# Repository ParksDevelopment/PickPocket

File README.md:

# 2Pocket

[Introduction](#Introduction)

[Info and Production](#Production)

[PCB](#PCB)

[Firmware](#Firmware)

[Case](#Case)

[Overview](#Overview)

## Introduciton

The PickPocket is a revamped version of my contest entry keyboard the [2Pocket](https://github.com/ParksDevelopment/2Pocket/tree/main). When I started making the list of changes I wanted to make it became clear to me I wanted to make a new project from the ground up, so despite thier similarities the PickPocket is a brand new project with the following features and changes from 2Pocket

Features
- 36 Kailh Choc V1 Low Profile Hot swap sockets (Using [Nocturnals](https://lowprokb.ca/collections/switches/products/ambients-silent-choc-switches) switches for all pictures)
- Bluetooth support between halves and computer
- Powered by 2 (XIAO nRF52840)[https://wiki.seeedstudio.com/XIAO_BLE/]
- 2 3.7V 1100 mAh batteries Charged through the USB C port on the back of each board
- ZMK and KMK compatibility tested
- Single reversible PCB for cheaper manufacturing
- Pass Through charging through magnetic push pins. Plugging in the left half and connecting the boards will charge both of them.
- Still small enough for your pockets!

Changes from 2Pocket
- Removed the pedometer. This was adding a few dollars per board and made the wiring for a reversable pcb more than I wanted to deal with
- Removed the 2 additional buttons. they were for pedometer controls primarily 
- Increased size for better case design. From 190mm x 74.8mm x 22mm to 207mm x 79mm x 23.5mm

The main goal of all these changes was to make something I could bring into work, was sturdy enough to be moved around, and solved my biggest frusteration with split keyboards which is charging them.

## Production

This project is both not for a contest and much simpler so I will briefly touch on the production and related information. Below is the Item list

| Part Name  | Quantity   | Solder by hand   |
|------------|------------|------------|
| 1N4148 Diode | 38| NO|
| 2 pin Jst socket | 2| YES|
| Choc hotswap sockets | 36| YES|
| Xiao NRF52840 | 2| YES|
| EEMB Lithium Polymer Battery 3.7V 1100mAh | 2| DNA|
|Magnetic Connector - Right Angle Three Contact Pins | 2| YES|

## PCB

The PCB has a footprint of 95mm x 71.5mm x 1.6mm and is reversable so the cost of production is quite small. It also features 4 mounting holes that are small enough to fit between the keys and are intended for M2 screws. Some things to note if you plan on making one is that to accomadate for the small size the parts that are hand soldered will always be on the bottom of their respective side. This means that you will want to put the micro controller on the bottom of each board. The wiring will work with it on the top but it will overlap with some of the keys. Same goes for the magnetic push pins. There are also 2 spots for the jst connectors. this is so they can be mounted on the bottom and still allow for the same ground power set up of a battery.

## Firmware

Due to the lack of a ADXL345 there is not much need for any firmware changes. Anything that works with a Xiao NRF52840 will work with this as long at it has bluetooth support

There are 2 pins, 4 and 5, which are also the I2C pins that go unused, for now. if you want to add the pedometer back in there is room for it through these.
Row Pins: 0,1,2,3
Column Pins: 6,7,8,9,10

## Case

The Case isn't anything special but I am happy with how it came out. Because of the extra space I have not working in the constraints of the contest I was able to get something a lot more sturdy. It is reversable like the board so 2 pieces each, a plate and the bottom. It also requires some threaded inserts but those can be easily removed. As it stands only the left side has a reset button.

| Part Name  | Quantity   | Link  |
|------------|------------|------------|
| M2 threaded inserts| 4| [Link](https://www.amazon.com/dp/B0DGP6FH5H?ref=nb_sb_ss_w_as-reorder_k1_1_7&amp=&crid=1JJC55YT0N74J&amp=&sprefix=m2+thre)|
| M2 Standoff and screws| 4| [Link](https://www.amazon.com/M2-Motherboard-Standoffs-Male-Female-Electronic/dp/B0BP6MT7RP/ref=sr_1_3?crid=1B0X8RUAJV7TB&dib=eyJ2IjoiMSJ9.4QcWRysCtdMoG_QF6B69rSAXRWaxghfNGHqr93WRVa_WalsyknAQGVyIgvgC3SLtFW8_Aq9xT8osy7Ujw2-KMYpiWbzHui2ul46HTimVXeC-CCfGhvA7aWc0ZlMaRxAaAogIQ04qn7LB9O_VYWGMlC1Eg_iei4z6oBYtRa2EqjSfnEmVXzc36kRT-TCwqZwGNqwdKtOXMUKBzJf1T8QhFMsNmuDVL8JtqZQa6X_zp2WqCpqts0BBzoPuzOpg5VYAeIQQLHLcRWSujUVZSC_JGGASAf63wpMIx7f5A5T_ZYg.Ff2cLg3y5jFBp4E5X0YNq7dlbfJBQw7yKhNeuV5YwsQ&dib_tag=se&keywords=m2%2Bstandoff%2Bkit&qid=1744292483&s=industrial&sprefix=m2%2Bstand%2Cindustrial%2C129&sr=1-3&th=1)

Much happier with the case this time around and while it still has quirks I don't feel the need to change it that much. I am using the keyboard to go to work and I never have any concerns throwing it in a bag.

## Overview

I have been happy with this redesign, while it is sad to lose the ADXL345, since there is a lot I was hoping to do with it and it was one of the more unique parts of the first board, it definetly made the project more streamlined, cheaper, and approachable. The pass through charging can not be understated for the impact it has made on my desire to make the board. The whole thing having "one" battery makes it much easier to work with. This is probably my last project with this form factor for a while, not because I don't like it but because I nailed what I was looking for with this one and don't have a whole lot I would want to change. Was told by multiple people it looks like legos, ie the photos.

If you enjoyed or found and of the information helpful consider [Buying me a coffee](https://buymeacoffee.com/parks) to keep working on projects like this!

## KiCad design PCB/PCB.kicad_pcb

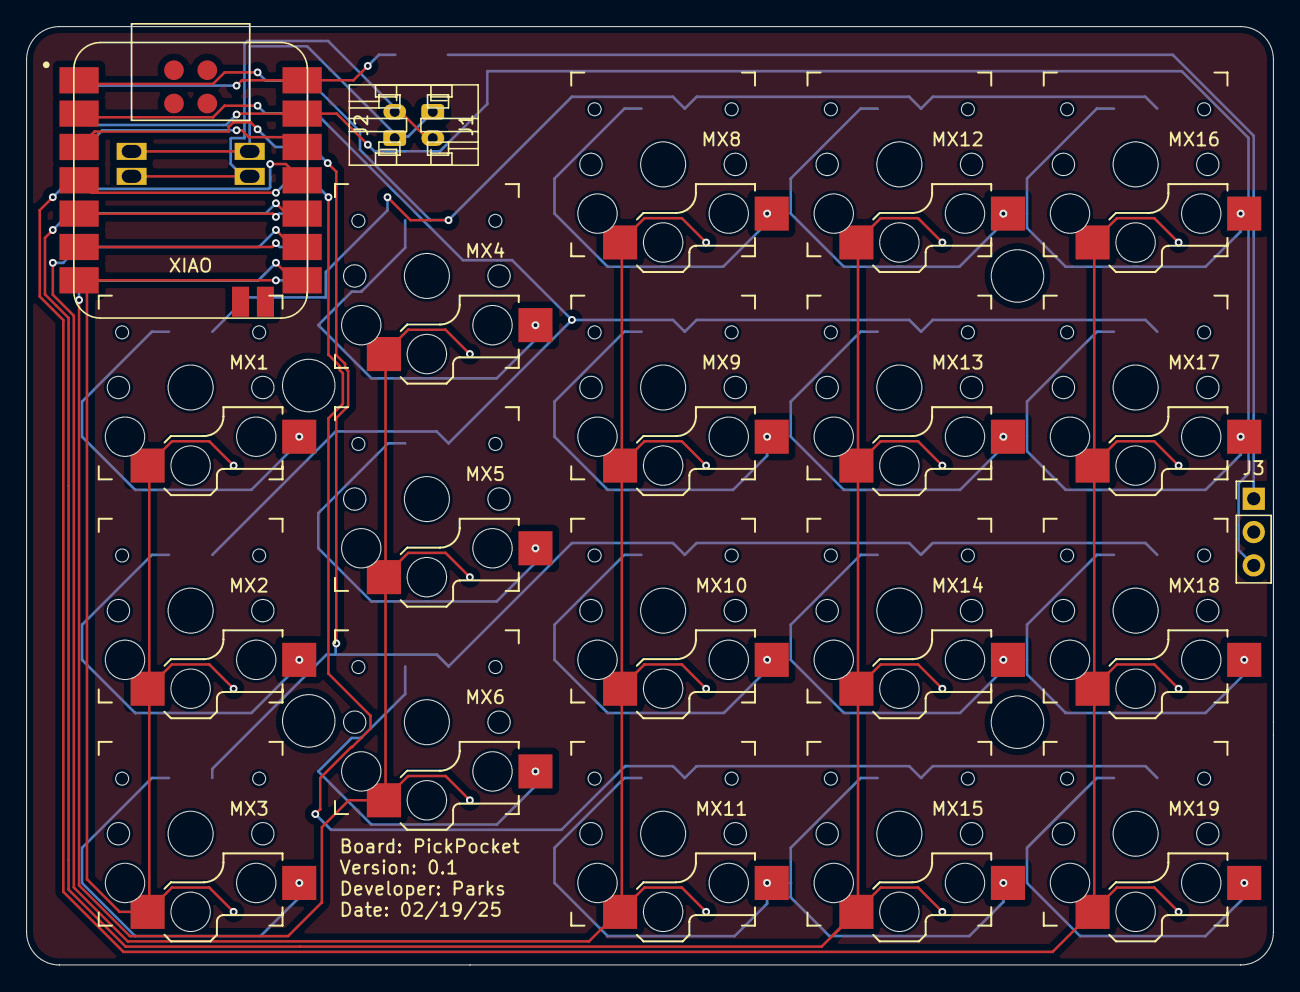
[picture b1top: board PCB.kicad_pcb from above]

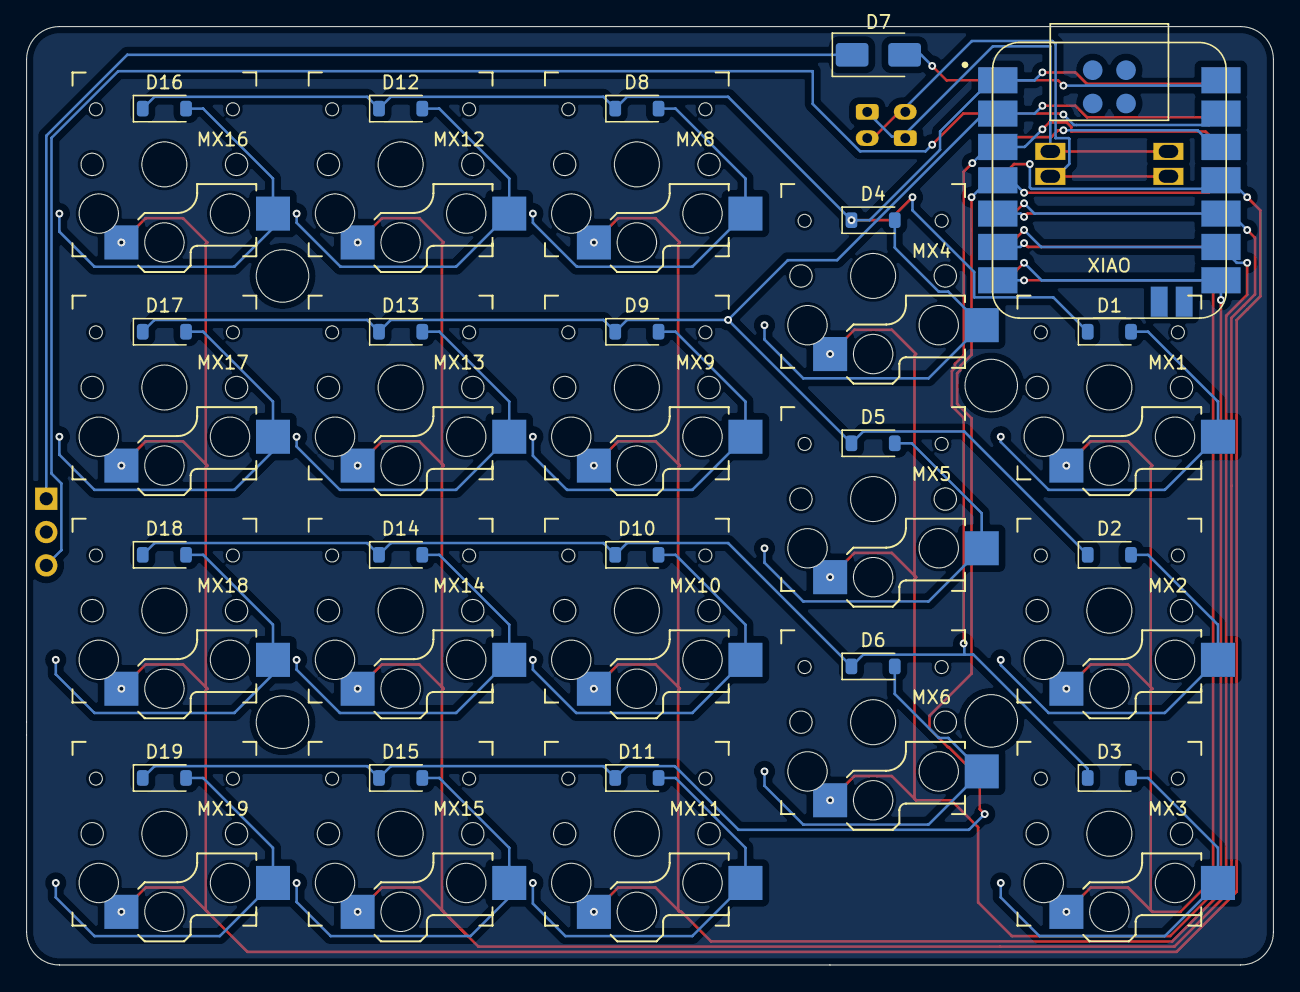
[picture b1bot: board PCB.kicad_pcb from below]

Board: 2 copper layers, 95.0 x 71.5 mm, 42 parts (20 on the bottom side), 35 nets.

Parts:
D1, D2, D3, D4, D5, D6, D8, D9, D10, D11, D12, D13, D14, D15, D16, D17, D18, D19: D_Small; D_SOD-123
D7: D_Schottky; D_SMA
J1, J2: Conn_01x02; JST_PH_S2B-PH-K_1x02_P2.00mm_Horizontal
J3: Conn_01x03; PinHeader_1x03_P2.54mm_Vertical
MX1, MX2, MX3, MX4, MX5, MX6, MX8, MX9, MX10, MX11, MX12, MX13, MX14, MX15, MX16, MX17, MX18, MX19: MX-NoLED; Kailh_socket_PG1350_reversible
U1, U2: Seeed Studio XIAO nRF52840; XIAO-nRF52840-Sense-14P-2.54-21X17.8MM

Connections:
+3.3V: U1.12 (3V3), U2.12 (3V3)
+5V: D7.2 (A), U1.14 (5V), U2.14 (5V)
/Bat+: J1.2, J2.2, U1.22 (BAT+), U2.22 (BAT+)
/Bat-: J1.1, J2.1, U1.21 (BAT-), U2.21 (BAT-)
/Col0: MX1.1 (COL), MX2.1 (COL), MX3.1 (COL), U1.7 (P1.11_D6_TX), U2.7 (P1.11_D6_TX)
/Col1: MX4.1 (COL), MX5.1 (COL), MX6.1 (COL), U1.8 (P1.12_D7_RX), U2.8 (P1.12_D7_RX)
/Col2: MX8.1 (COL), MX9.1 (COL), MX10.1 (COL), MX11.1 (COL), U1.9 (P1.13_D8_SCK), U2.9 (P1.13_D8_SCK)
/Col3: MX12.1 (COL), MX13.1 (COL), MX14.1 (COL), MX15.1 (COL), U1.10 (P1.14_D9_MISO), U2.10 (P1.14_D9_MISO)
/Col4: MX16.1 (COL), MX17.1 (COL), MX18.1 (COL), MX19.1 (COL), U1.11 (P1.15_D10_MOSI), U2.11 (P1.15_D10_MOSI)
/Row0: D1.1 (K), D4.1 (K), D8.1 (K), D12.1 (K), D16.1 (K), U1.1 (P0.02_A0_D0), U2.1 (P0.02_A0_D0)
/Row1: D2.1 (K), D5.1 (K), D9.1 (K), D13.1 (K), D17.1 (K), U1.2 (P0.03_A1_D1), U2.2 (P0.03_A1_D1)
/Row2: D3.1 (K), D6.1 (K), D10.1 (K), D14.1 (K), D18.1 (K), U1.3 (P0.28_A2_D2), U2.3 (P0.28_A2_D2)
/Row3: D11.1 (K), D15.1 (K), D19.1 (K), U1.4 (P0.29_A3_D3), U2.4 (P0.29_A3_D3)
/temp1: U1.5 (P0.04_A4_D4_SDA), U2.5 (P0.04_A4_D4_SDA)
/temp2: U1.6 (P0.05_A5_D5_SCL), U2.6 (P0.05_A5_D5_SCL)
GND: J3.3, U1.13 (GND), U2.13 (GND)
unnamed: D1.2 (A), MX1.2 (ROW)
unnamed: D2.2 (A), MX2.2 (ROW)
unnamed: D3.2 (A), MX3.2 (ROW)
unnamed: D4.2 (A), MX4.2 (ROW)
unnamed: D5.2 (A), MX5.2 (ROW)
unnamed: D6.2 (A), MX6.2 (ROW)
unnamed: D7.1 (K), J3.1
unnamed: D8.2 (A), MX8.2 (ROW)
unnamed: D9.2 (A), MX9.2 (ROW)
unnamed: D10.2 (A), MX10.2 (ROW)
unnamed: D11.2 (A), MX11.2 (ROW)
unnamed: D12.2 (A), MX12.2 (ROW)
unnamed: D13.2 (A), MX13.2 (ROW)
unnamed: D14.2 (A), MX14.2 (ROW)
unnamed: D15.2 (A), MX15.2 (ROW)
unnamed: D16.2 (A), MX16.2 (ROW)
unnamed: D17.2 (A), MX17.2 (ROW)
unnamed: D18.2 (A), MX18.2 (ROW)
unnamed: D19.2 (A), MX19.2 (ROW)

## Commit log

2025-02-13 first
2025-02-20 pcb v0.1
2025-04-10 updates made to the case
2025-04-10 pictures
2025-04-16 Create LICENSE
